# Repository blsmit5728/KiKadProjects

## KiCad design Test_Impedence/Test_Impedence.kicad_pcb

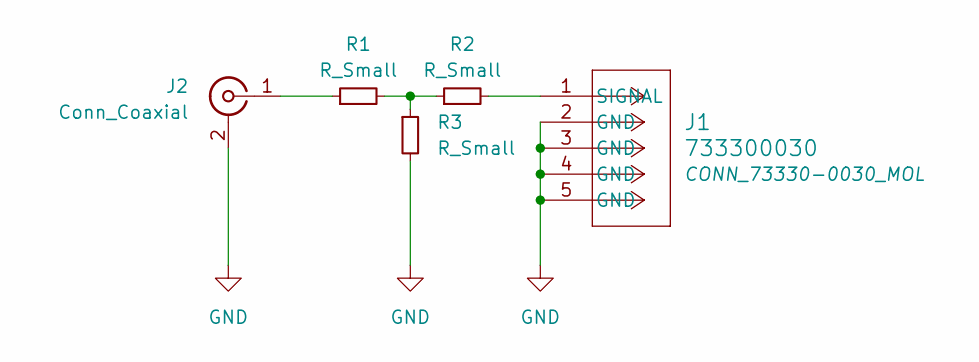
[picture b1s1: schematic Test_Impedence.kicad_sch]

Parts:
J1: 733300030; CONN_73330-0030_MOL
J2: Conn_Coaxial; SMA_Amphenol_901-143_Horizontal
R1, R2, R3: R_Small; R_1206_3216Metric

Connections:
GND: J1.2 (GND), J1.3 (GND), J1.4 (GND), J1.5 (GND), J2.2 (Ext), R3.2
unnamed: J1.1 (SIGNAL), R2.2
unnamed: J2.1 (In), R1.1
unnamed: R1.2, R2.1, R3.1

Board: 2 copper layers, 5 parts (0 on the bottom side), 4 nets, no tracks yet.

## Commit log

2026-03-18 Added Test Impedence Project
